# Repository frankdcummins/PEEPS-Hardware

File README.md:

# PEEPS-Hardware
Repository for the Northwestern University Segal Design School Students' Positive End Expiration Pressure (PEEP) project hardware.

## Description
This printed circuit board (PCB) is designed to make use of NXP's [MPXV7002 Integrated Silicon Pressure Sensor](https://www.nxp.com/docs/en/data-sheet/MPXV7002.pdf) to measure and record pressure at as many as two points in the PEEP apparatus. It also includes a simple driver for an [air pump](https://www.adafruit.com/product/4699) that can generate up to 2.5 L/min of air flow. The microcontroller takes pressure readings at 100Hz and transmits them over a serial UART port to be analyzed in real-time or offline. The controller can activate the air pump through this serial interface as well. <br><br>This board will be used to verify the student design's functionality against the industry standard. It uses primarily through-hole components for ease and speed of assembly.

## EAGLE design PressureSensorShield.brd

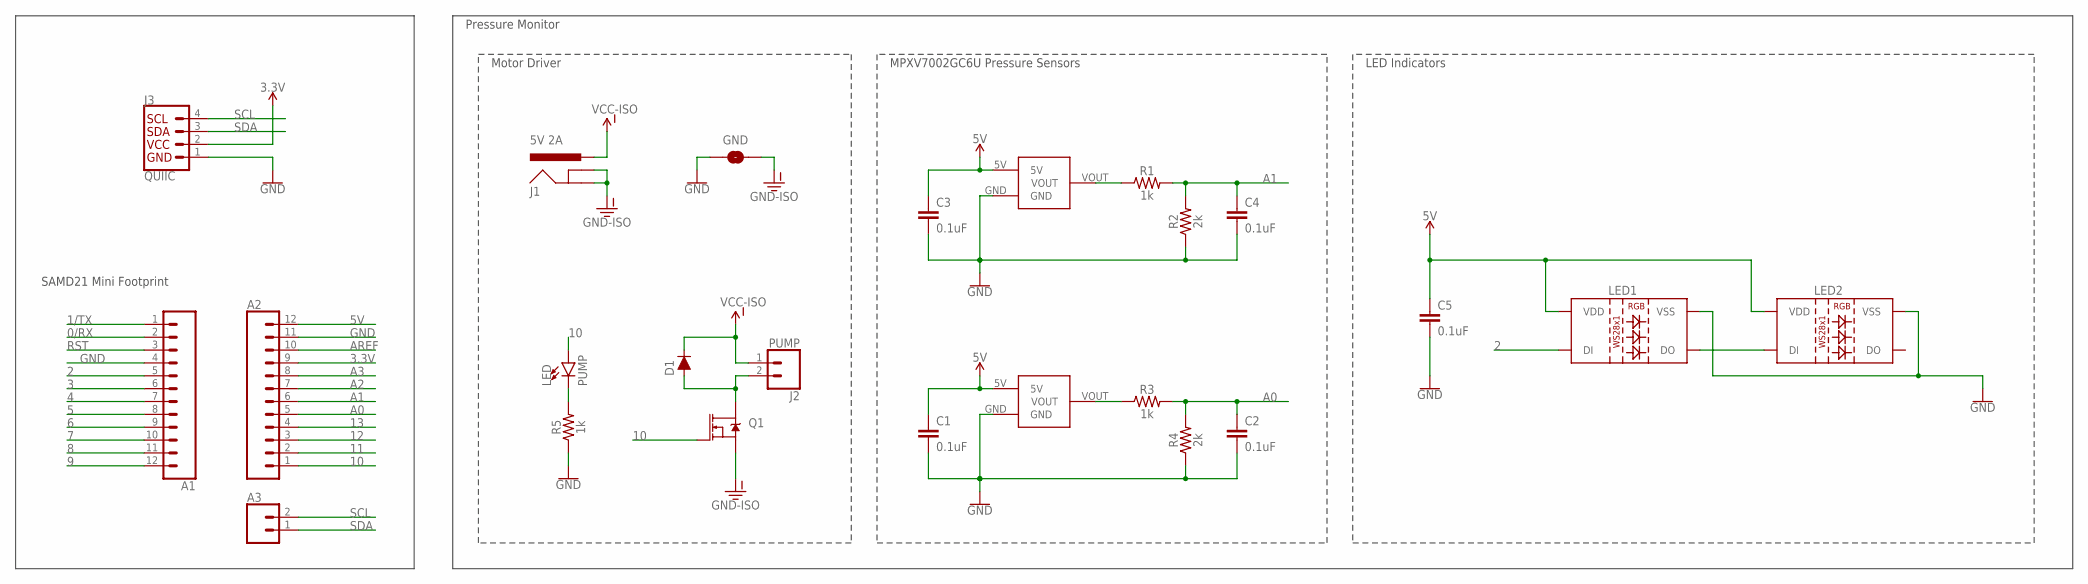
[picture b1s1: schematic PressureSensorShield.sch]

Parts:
A1, A2: CONN_12; 1X12
A3: CONN_02; 1X02
C1, C2, C3, C4, C5: 0.1uF; CAP-PTH-SMALL-KIT
D1: DIODE-KIT; DIODE-1N4148-KIT
GND: JUMPER-SMT_2_NO_NO-SILK; SMT-JUMPER_2_NO_NO-SILK
J1: 5V 2A; POWER_JACK_PTH
J2: PUMP; SCREWTERMINAL-3.5MM-2
J3: QUIIC; JST04_1MM_RA
LED: PUMP; LED_3MM
LED1, LED2: WS2812B
Q1: MOSFET-NCH-FQP30N06L; TO220V
R1, R3, R5: 1k; AXIAL-0.3-KIT
R2, R4: 2k; AXIAL-0.3-KIT
SENSOR: SENSOR 1; SMALL_OUTLINE
SENSOR2: SENSOR 2; SMALL_OUTLINE

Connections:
0/RX: A1.2
1/TX: A1.1
2: A1.5, LED1.4 (DI)
3: A1.6
3.3V: A2.9, J3.2
4: A1.7
5: A1.8
5V: A2.12, C1.1, C3.1, C5.1, LED1.1 (VDD), LED2.1 (VDD), SENSOR.5V, SENSOR2.5V
6: A1.9
7: A1.10
8: A1.11
9: A1.12
10: A2.1, LED.A, Q1.1 (G)
11: A2.2
12: A2.3
13: A2.4
A0: A2.5, C2.1, R3.P$2 (2), R4.P$2 (2)
A1: A2.6, C4.1, R1.P$2 (2), R2.P$2 (2)
A2: A2.7
A3: A2.8
AREF: A2.10
GND: A1.4, A2.11, C1.2, C2.2, C3.2, C4.2, C5.2, GND.1, J3.1, LED1.3 (VSS), LED2.3 (VSS), R2.P$1 (1), R4.P$1 (1), R5.P$1 (1), SENSOR.GND, SENSOR2.GND
GND-ISO: GND.2, J1.GND, J1.GNDBREAK, Q1.3 (S)
unnamed: LED.K (C), R5.P$2 (2)
unnamed: R1.P$1 (1), SENSOR2.VOUT
unnamed: LED1.2 (DO), LED2.4 (DI)
unnamed: R3.P$1 (1), SENSOR.VOUT
unnamed: D1.A, J2.2, Q1.2 (D)
RST: A1.3
SCL: A3.2, J3.4
SDA: A3.1, J3.3
VCC-ISO: D1.C, J1.PWR, J2.1

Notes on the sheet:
LED Indicators
Pressure Monitor
SAMD21 Mini Footprint
Motor Driver
MPXV7002GC6U Pressure Sensors

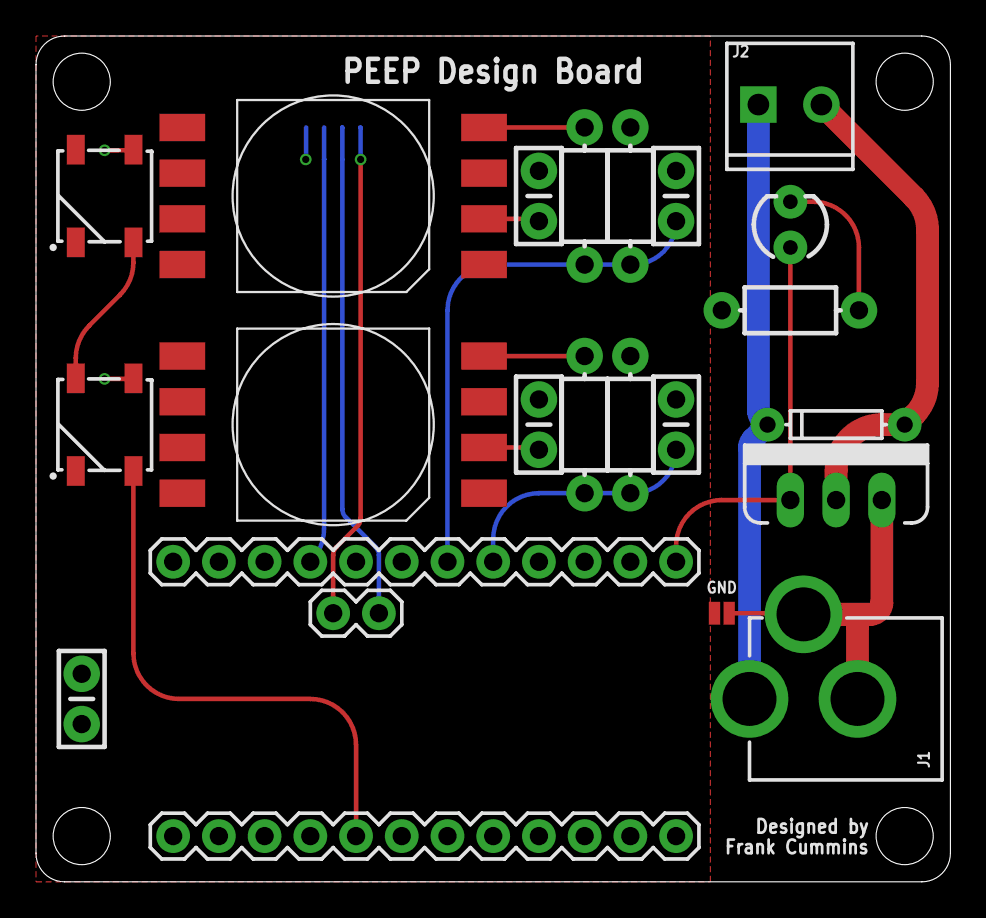
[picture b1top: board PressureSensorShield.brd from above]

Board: 2 copper layers, 50.8 x 47.0 mm, 24 parts (1 on the bottom side), 16 nets.

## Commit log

2021-03-20 Updated: - Added photo to README
    -Frank

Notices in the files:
parts and their libraries:
SparkFun-Connectors: Licensing: Creative Commons ShareAlike 4.0 International - https://creativecommons.org/licenses/by-sa/4.0
